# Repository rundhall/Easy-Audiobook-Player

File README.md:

# Easy Audiobook Player

## Introduction
The **Easy Audiobook Player** is a simple, user-friendly device designed for individuals who face challenges using modern gadgets. Originally created as a Christmas gift for my 94-year-old grandmother, this device is tailored for users with visual or physical impairments, providing an accessible solution for audiobook playback.

---

## Features
- **Single Button Operation**: Simple start/stop functionality.
- **Advanced Controls**:
  - 5-second press: Skip to the next audiobook file.
  - 20-second press: Restart playback from the beginning.
- **Resume Playback**: Automatically resumes from the last played position.

---

## Components

| Component                                    | Quantity | Link                                                                 | Price  |
|---------------------------------------------|----------|----------------------------------------------------------------------|--------|
| DC 12V 24V 80W x 2 Audio Amplifier Board    | 1        | [Link](https://www.aliexpress.com/item/32823374190.html)             | $2.91  |
| Arduino Nano 16MHz ATMEGA328P               | 1        | [Link](https://www.aliexpress.com/item/1005006472755752.html)        | $3.32  |
| DFPlayer Mini MP3 Module                    | 1        | [Link](https://www.aliexpress.com/item/4000379417594.html)           | $1.63  |
| Game Push Button Switch                     | 1        | [Link](https://www.aliexpress.com/item/1005006347986280.htm)         | $0.50  |
| Wooden Enclosure Box (16x10x9.2 cm)         | 1        | [Link](https://www.aliexpress.com/item/1005005854034476.html)        | $4.94  |
| Toggle Switch SS22D07 2P2T                  | 1        | [Link](https://www.aliexpress.com/item/32822779479.html)             | $0.91  |
| USB 2.0 A Power Supply Extension Cable      | 1        | [Link](https://www.aliexpress.com/item/1005004980471643.html)        | $0.56  |
| DC-DC Voltage Regulator Module LM2596S      | 1        | [Link](https://www.aliexpress.com/item/1005001691110030.html)        | $0.72  |
| GHXAMP Full Range Speakers (4 ohm, 16W)     | 2        | [Link](https://www.aliexpress.com/item/1005007219657143.html)        | $7.31  |
| Mini Screw Terminal Blocks                  | 1        | [Link](https://www.aliexpress.com/item/1005005433827504.html)        | $0.72  |
| Micro SD Card (max. 32 GB)                  | 1        | [Link](https://www.aliexpress.com/item/1005001617961938.html)        | $2.57  |
| PCB                                         | 1        | Custom                                                               | ~$10.00 |

**Total Material Cost**: $36.09

---

## Assembly
### Hardware
1. **Connect Components**: Use a custom PCB or breadboard for wiring the Arduino Nano, DFPlayer Mini, and amplifier board.
2. **Enclosure**:
   - Drill holes for the speaker, button, and cable entry.
   - Mount all components securely in the wooden box.
3. **Power Supply**: Feed the USB power cable through the enclosure and connect to a 5V charger.

### Software
#### Preparing MP3 Files
1. Place your audiobook MP3 files into a `mp3_files` folder.
2. Use the provided Python script (`mp3_to_mp3chunks.bat`) to split files into 5-minute chunks.
3. Copy the output files to the `01` folder on a FAT32-formatted SD card.

#### Programming the Arduino
1. Install [PlatformIO](https://platformio.org/) in Visual Studio Code.
2. Clone the repository and open the `EasyAudiobookPlayer_Arduino` project.
3. Update the `platformio.ini` file to match your Arduino Nano configuration.
4. Upload the code to the Arduino Nano using PlatformIO.

---

## How It Works
- **Playback**: The Arduino controls the DFPlayer Mini to play audio files stored on the SD card.
- **Amplification**: The audio signal is amplified and played through the speakers.
- **Power Management**: A DC-DC converter steps up voltage for the amplifier, while the Arduino and DFPlayer operate on 5V.

---

## Usage Instructions
1. Press the button to start or stop playback.
2. Hold for 5 seconds to skip to the next file.
3. Hold for 20 seconds to reset playback.
4. Enjoy your audiobook!

---

## Conclusion
This Easy Audiobook Player is a thoughtful gift for anyone who values simplicity and accessibility. Whether for a loved one or as a DIY project, it’s a functional and meaningful creation.

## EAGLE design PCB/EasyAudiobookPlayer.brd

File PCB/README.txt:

# PCB for the Easy Audiobook Player

This is the wiring diagram and PCB plan for Easy Audiobook Player project to make this project even easier to build.

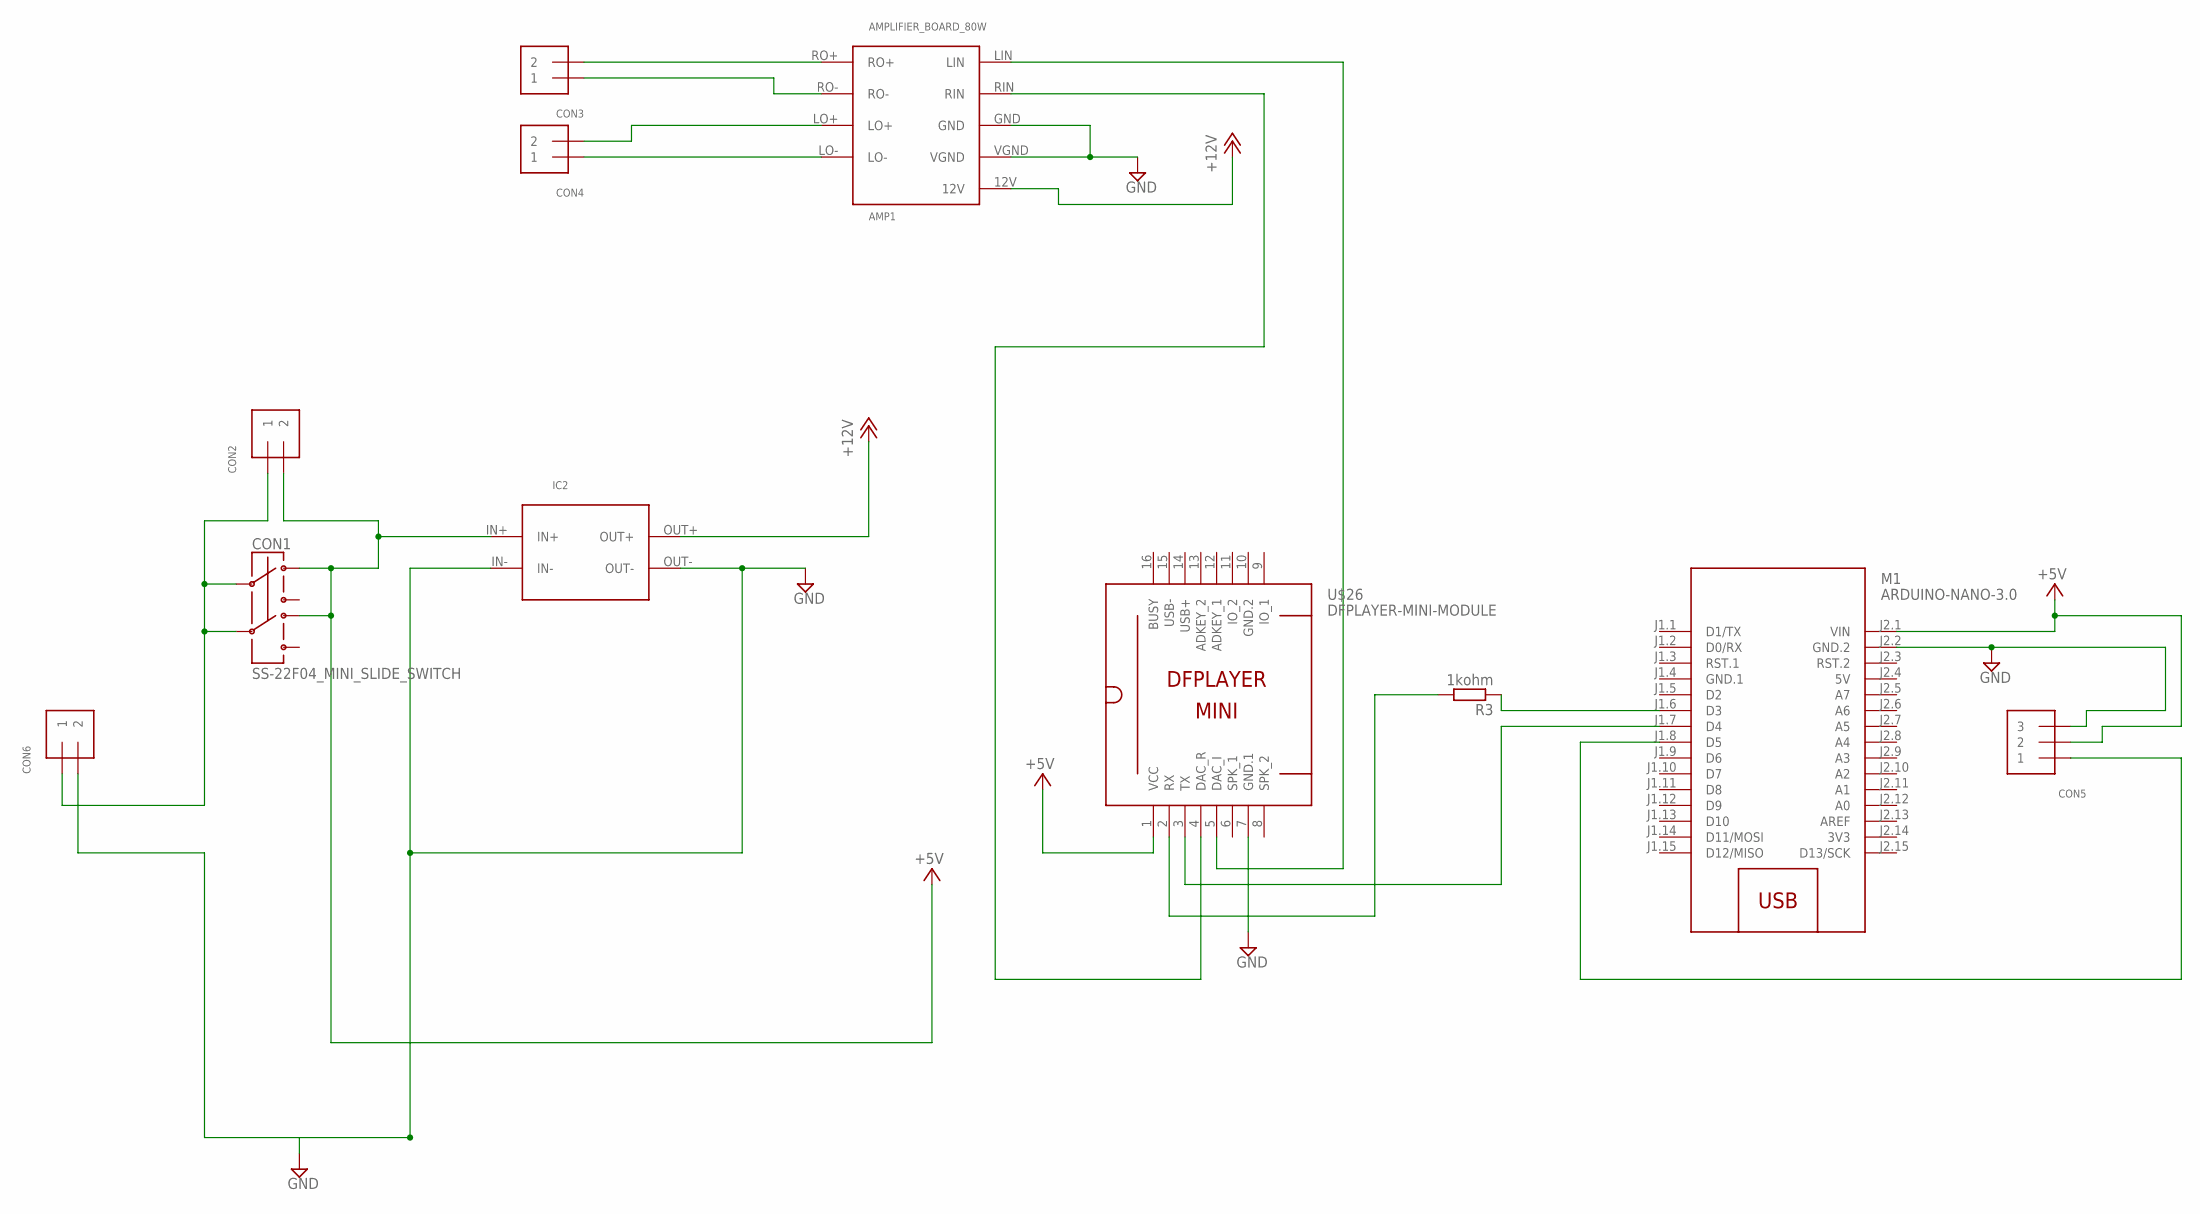
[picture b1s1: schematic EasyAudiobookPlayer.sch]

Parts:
AMP1: AMPLIFIER_BOARD_80W
CON1: SS-22F04_MINI_SLIDE_SWITCH
CON2, CON3, CON4, CON6: 1X2_5MM_TERMINAL_BLOCK
CON5: 1X3_5MM_TERMINAL_BLOCK
IC2: XL6009_STEP_UP_CONVERTER_MODULE
M1: ARDUINO-NANO-3.0
R3: 1kohm; M1206
U$26: DFPLAYER-MINI-MODULE

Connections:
3V3: M1.J2.14 (3V3)
5V: M1.J2.4 (5V)
+5V: CON1.O1_2, CON1.O2_2, CON2.2, CON5.2, IC2.IN+, M1.J2.1 (VIN), U$26.1 (VCC)
+12V: AMP1.12V, IC2.OUT+
GND: AMP1.GND, AMP1.VGND, CON5.3, CON6.2, IC2.IN-, IC2.OUT-, M1.J2.2 (GND.2), U$26.7 (GND.1)
GND.1: M1.J1.4 (GND.1)
GND.2: U$26.10 (GND.2)
unnamed: CON1.I1_1, CON1.I2_1, CON2.1, CON6.1
unnamed: AMP1.RO+, CON3.2
unnamed: AMP1.RO-, CON3.1
unnamed: AMP1.LO+, CON4.2
unnamed: AMP1.LO-, CON4.1
unnamed: M1.J1.6 (D3), R3.1
unnamed: R3.2, U$26.2 (RX)
unnamed: M1.J1.7 (D4), U$26.3 (TX)
unnamed: AMP1.RIN, U$26.4 (DAC_R)
unnamed: AMP1.LIN, U$26.5 (DAC_I)
unnamed: CON5.1, M1.J1.8 (D5)

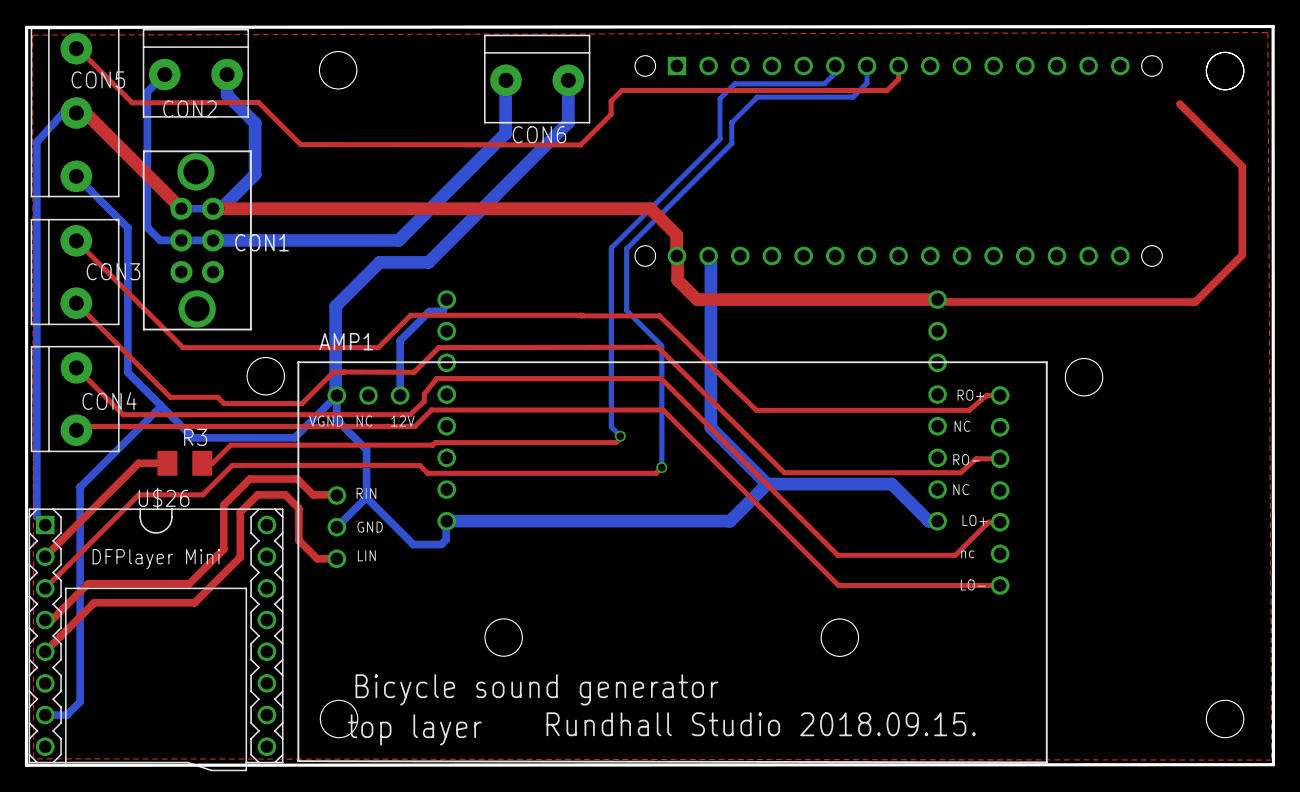
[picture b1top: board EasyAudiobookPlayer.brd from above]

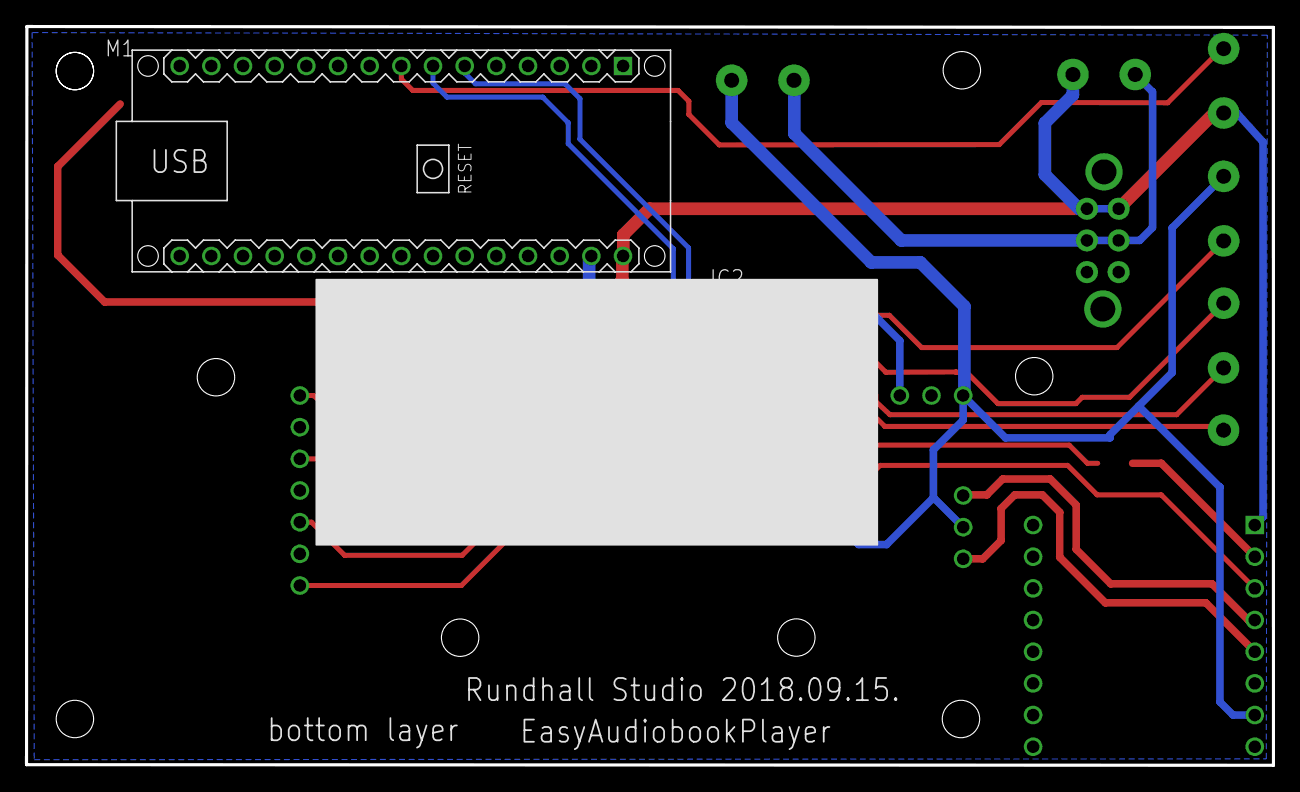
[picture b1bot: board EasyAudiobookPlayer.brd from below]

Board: 4 copper layers, 100.0 x 59.3 mm, 11 parts (2 on the bottom side), 14 nets.

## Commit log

2024-11-25 first submit
2024-11-25 Dir change
2024-11-28 next track bug fix

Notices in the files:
parts and their libraries:
diy-modules: Released under the Creative Commons Attribution 4.0 International License: http://creativecommons.org/licenses/by/4.0
